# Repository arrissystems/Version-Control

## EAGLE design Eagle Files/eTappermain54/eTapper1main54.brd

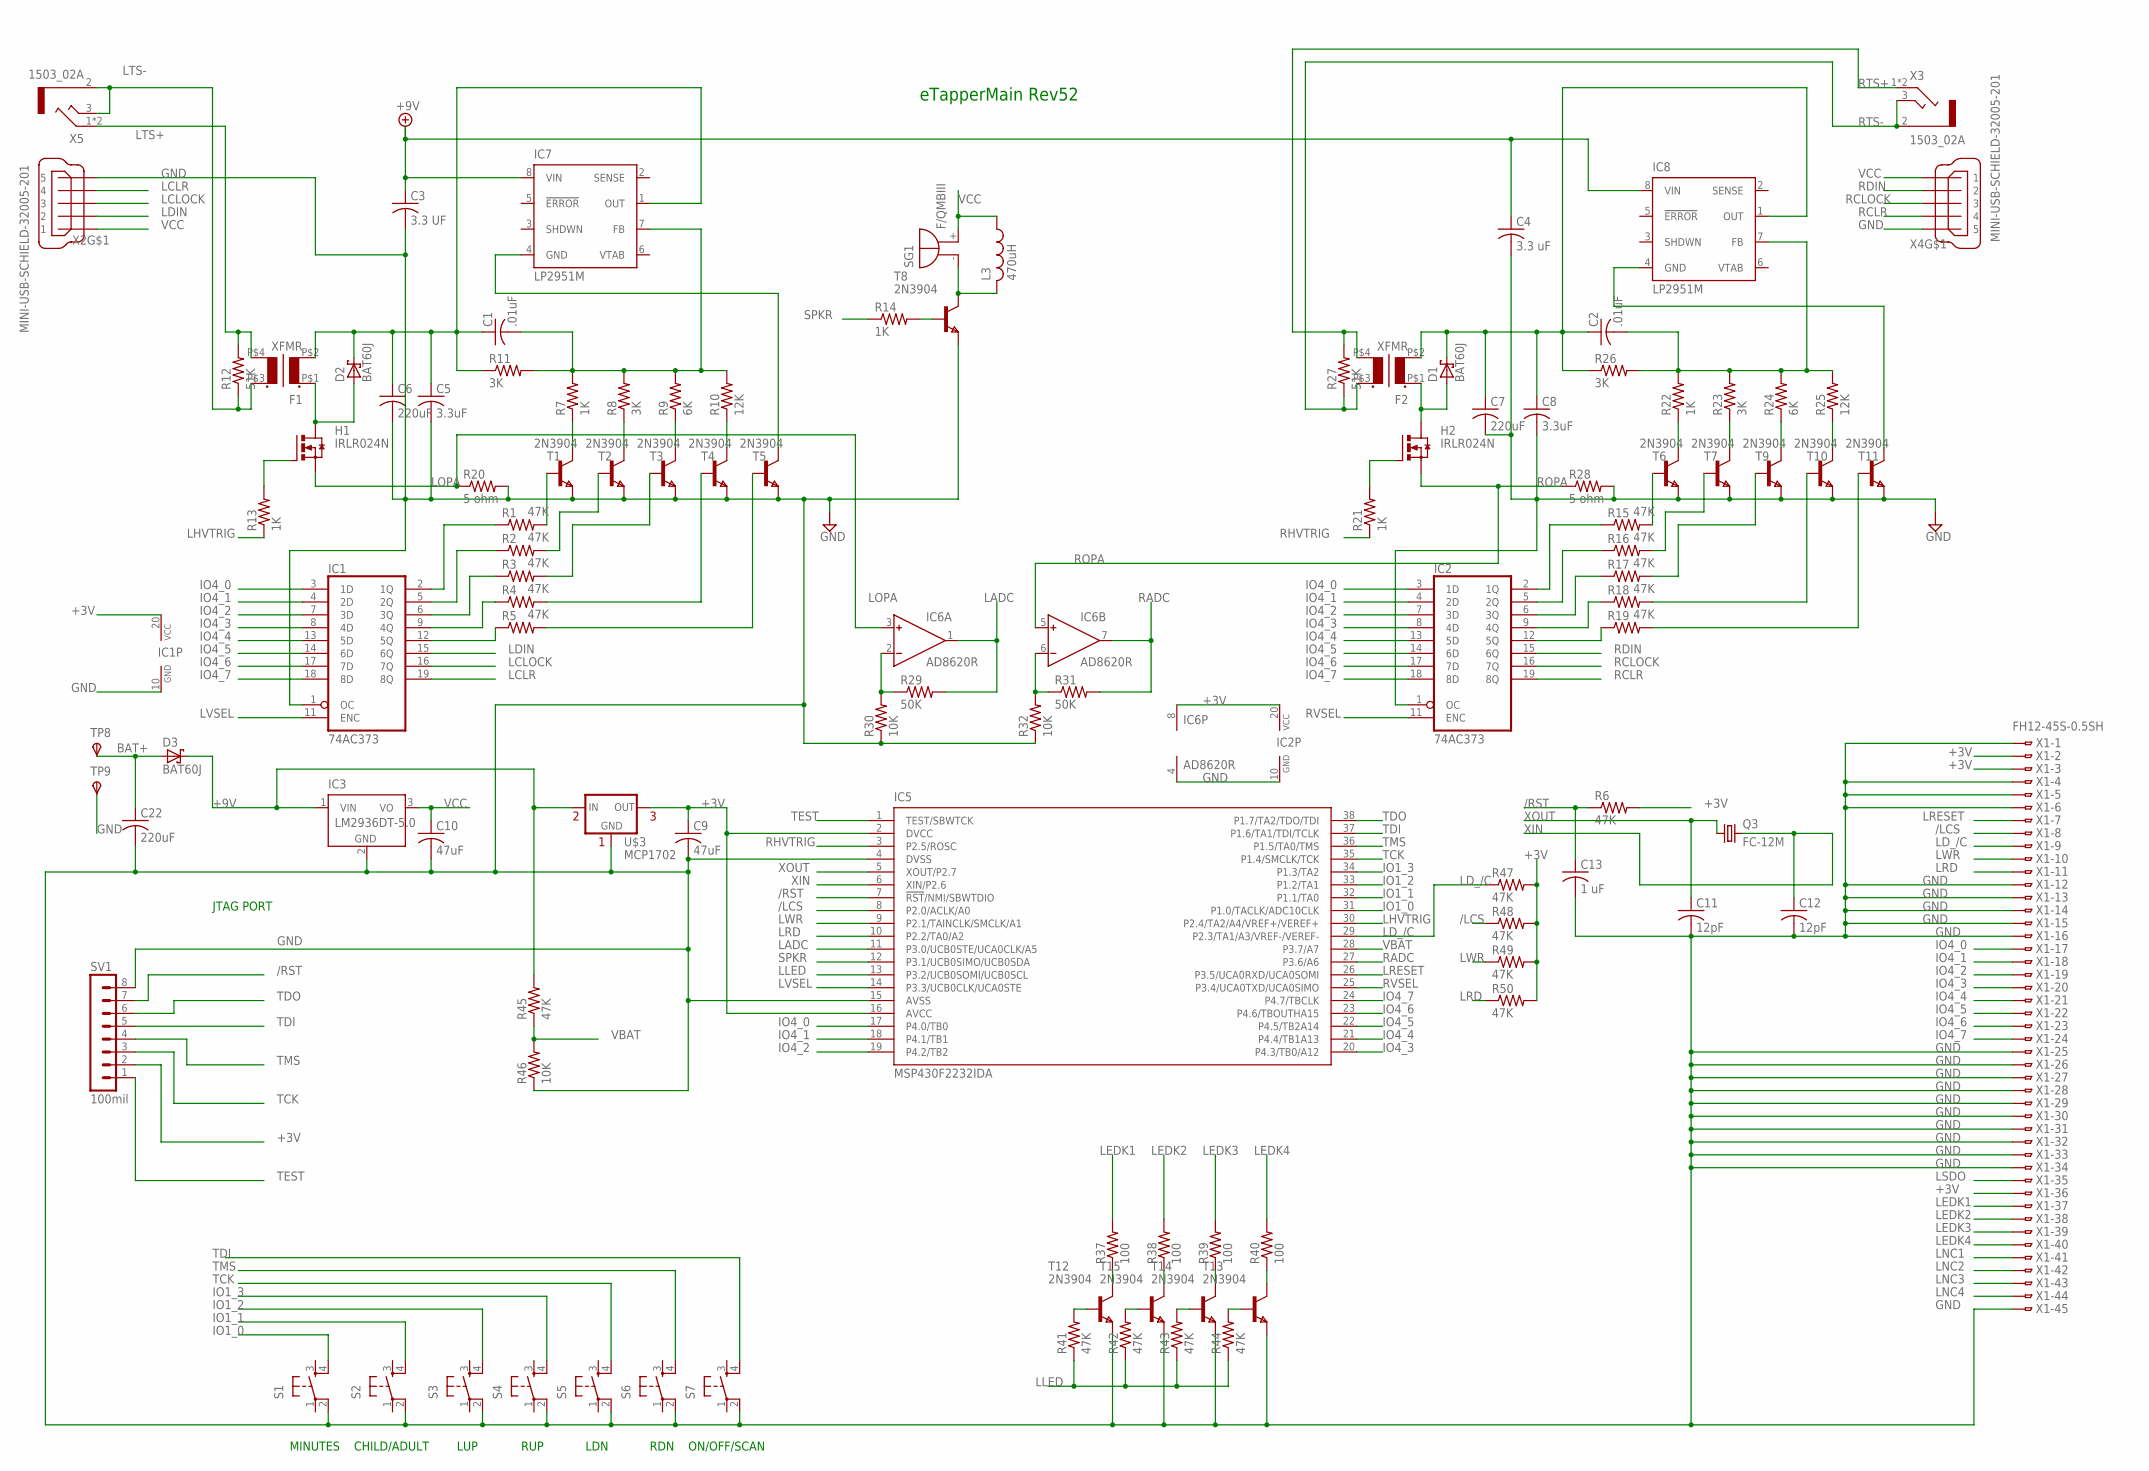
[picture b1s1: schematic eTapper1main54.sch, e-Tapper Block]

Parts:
C1, C2: .01uF; C0805
C3: 3.3 UF; C1206
C4: 3.3 uF; C1206
C5, C8: 3.3uF; C0805
C6, C7, C22: 220uF; C1206
C9, C10: 47uF; C1206
C11, C12: 12pF; C0805
C13: 1 uF; C0805
D1, D2, D3: BAT60J; SOD323_ST
F1, F2: XFMR
H1, H2: IRLR024N; D-PAK_TO252AA
IC1, IC2: 74AC373; SO20
IC3: LM2936DT-5.0; TO252
IC5: MSP430F2232IDA; TSSOP38_R-PDSO-G38-DA
IC6: AD8620R; SO8
IC7, IC8: LP2951M; SO08
L3: 470uH; L2825P
Q3: FC-12M
R1, R2, R3, R4, R5, R6, R15, R16, R17, R18, R19, R41, R42, R43, R44, R45, R47, R48, R49, R50: 47K; R0603
R7, R13, R14, R21, R22: 1K; R0603
R8, R11, R23, R26: 3K; R0603
R9, R24: 6K; R0603
R10, R25: 12K; R0603
R12, R27: 51K; R0603
R20, R28: 5 ohm; R0603
R29, R31: 50K; R0603
R30, R32, R46: 10K; R0603
R37, R38, R39, R40: 100; R0603
S1, S2, S3, S4, S5, S6, S7: 10-XX; B3F-10XX
SG1: F/QMBIII
SV1: 100mil; MA08-1
T1, T2, T3, T4, T5, T6, T7, T8, T9, T10, T11, T12, T13, T14, T15: 2N3904; SOT-23
TP8, TP9: TPSPAD1-20; P1-20
U$3: MCP1702; TO92-
X1: FH12-45S-0.5SH
X2, X4: MINI-USB-SCHIELD-32005-201; 32005-201
X3, X5: 1503_02A; 1503_02

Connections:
+3V: C9.1, IC1.20 (VCC), IC2.20 (VCC), IC5.2 (DVCC), IC5.16 (AVCC), IC6.8 (V+), R6.2, R47.2, R48.2, R49.2, R50.2, SV1.2, U$3.3 (OUT), X1.2, X1.3, X1.36
+9V: C3.1, C4.1, D3.C, IC3.1 (VIN), IC7.8 (VIN), IC8.8 (VIN), R45.2, U$3.2 (IN)
/LCS: IC5.8 (P2.0/ACLK/A0), R48.1, X1.8
/RST: C13.1, IC5.7 (!RST!/NMI/SBWTDIO), R6.1, SV1.7
BAT+: C22.1, D3.A, TP8.TP
GND: C3.2, C4.2, C5.2, C6.2, C7.2, C8.2, C9.2, C10.2, C11.2, C12.2, C13.2, C22.2, IC1.1 (OC), IC1.10 (GND), IC2.1 (OC), IC2.10 (GND), IC3.2 (GND), IC5.4 (DVSS), IC5.15 (AVSS), IC6.4 (V-), R20.2, R28.2, R30.1, R32.1, R46.1, S1.2 (P1), S2.2 (P1), S3.2 (P1), S4.2 (P1), S5.2 (P1), S6.2 (P1), S7.2 (P1), SV1.8, T1.2 (E), T2.2 (E), T3.2 (E), T4.2 (E), T5.2 (E), T6.2 (E), T7.2 (E), T8.2 (E), T9.2 (E), T10.2 (E), T11.2 (E), T12.2 (E), T13.2 (E), T14.2 (E), T15.2 (E), TP9.TP, U$3.1 (GND), X1.1, X1.4, X1.5, X1.6, X1.12, X1.13, X1.14, X1.15, X1.16, X1.25, X1.26, X1.27, X1.28, X1.29, X1.30, X1.31, X1.32, X1.33, X1.34, X1.45, X2.5, X4.5
IO1_0: IC5.31 (P1.0/TACLK/ADC10CLK), S1.4 (S1)
IO1_1: IC5.32 (P1.1/TA0), S2.4 (S1)
IO1_2: IC5.33 (P1.2/TA1), S3.4 (S1)
IO1_3: IC5.34 (P1.3/TA2), S4.4 (S1)
IO4_0: IC1.3 (1D), IC2.3 (1D), IC5.17 (P4.0/TB0), X1.17
IO4_1: IC1.4 (2D), IC2.4 (2D), IC5.18 (P4.1/TB1), X1.18
IO4_2: IC1.7 (3D), IC2.7 (3D), IC5.19 (P4.2/TB2), X1.19
IO4_3: IC1.8 (4D), IC2.8 (4D), IC5.20 (P4.3/TB0/A12), X1.20
IO4_4: IC1.13 (5D), IC2.13 (5D), IC5.21 (P4.4/TB1A13), X1.21
IO4_5: IC1.14 (6D), IC2.14 (6D), IC5.22 (P4.5/TB2A14), X1.22
IO4_6: IC1.17 (7D), IC2.17 (7D), IC5.23 (P4.6/TBOUTHA15), X1.23
IO4_7: IC1.18 (8D), IC2.18 (8D), IC5.24 (P4.7/TBCLK), X1.24
LADC: IC5.11 (P3.0/UCB0STE/UCA0CLK/A5), IC6.1 (OUT), R29.2
LCLOCK: IC1.16 (7Q), X2.3
LCLR: IC1.19 (8Q), X2.4
LDIN: IC1.15 (6Q), X2.2
LD_/C: IC5.29 (P2.3/TA1/A3/VREF-/VEREF-), R47.1, X1.9
LEDK1: R37.2, X1.37
LEDK2: R38.2, X1.38
LEDK3: R39.2, X1.39
LEDK4: R40.2, X1.40
LHVTRIG: IC5.30 (P2.4/TA2/A4/VREF+/VEREF+), R13.1
LLED: IC5.13 (P3.2/UCB0SOMI/UCB0SCL), R41.1, R42.1, R43.1, R44.1
LNC1: X1.41
LNC2: X1.42
LNC3: X1.43
LNC4: X1.44
LOPA: H1.3 (S), IC6.3 (IN+), R20.1
LRD: IC5.10 (P2.2/TA0/A2), R50.1, X1.11
LRESET: IC5.26 (P3.5/UCA0RXD/UCA0SOMI), X1.7
LSDO: X1.35
LTS+: F1.P$4 (S2), R12.2, X5.1 (2), X5.4 (2)
LTS-: F1.P$3 (S1), R12.1, X5.2 (1), X5.3
LVSEL: IC1.11 (ENC), IC5.14 (P3.3/UCB0CLK/UCA0STE)
LWR: IC5.9 (P2.1/TAINCLK/SMCLK/A1), R49.1, X1.10
unnamed: IC1.2 (1Q), R1.1
unnamed: IC1.5 (2Q), R2.1
unnamed: IC1.6 (3Q), R3.1
unnamed: IC1.9 (4Q), R4.1
unnamed: IC1.12 (5Q), R5.1
unnamed: L3.2, SG1.- (+), T8.1 (C)
unnamed: R4.2, T4.3 (B)
unnamed: R5.2, T5.3 (B)
unnamed: D2.A, F1.P$1 (P1), H1.4 (D)
unnamed: R7.1, T1.1 (C)
unnamed: R8.1, T2.1 (C)
unnamed: R9.1, T3.1 (C)
unnamed: R1.2, T1.3 (B)
unnamed: R2.2, T2.3 (B)
unnamed: R3.2, T3.3 (B)
unnamed: R10.1, T4.1 (C)
unnamed: C1.2, IC7.7 (FB), R7.2, R8.2, R9.2, R10.2, R11.2
unnamed: C1.1, C5.1, C6.1, D2.C, F1.P$2 (P2), IC7.1 (OUT), R11.1
unnamed: D1.A, F2.P$1 (P1), H2.4 (D)
unnamed: IC2.2 (1Q), R15.1
unnamed: H1.1 (G), R13.2
unnamed: R14.2, T8.3 (B)
unnamed: IC2.5 (2Q), R16.1
unnamed: IC2.6 (3Q), R17.1
unnamed: IC2.9 (4Q), R18.1
unnamed: IC2.12 (5Q), R19.1
unnamed: R44.2, T13.3 (B)
unnamed: R15.2, T6.3 (B)
unnamed: R16.2, T7.3 (B)
unnamed: R17.2, T9.3 (B)
unnamed: R18.2, T10.3 (B)
unnamed: R19.2, T11.3 (B)
unnamed: R22.1, T6.1 (C)
unnamed: R23.1, T7.1 (C)
unnamed: R24.1, T9.1 (C)
unnamed: R25.1, T10.1 (C)
unnamed: C2.2, IC8.7 (FB), R22.2, R23.2, R24.2, R25.2, R26.2
unnamed: C2.1, C7.1, C8.1, D1.C, F2.P$2 (P2), IC8.1 (OUT), R26.1
unnamed: R37.1, T12.1 (C)
unnamed: H2.1 (G), R21.2
unnamed: R38.1, T15.1 (C)
unnamed: R39.1, T14.1 (C)
unnamed: IC7.4 (GND), T5.1 (C)
unnamed: R40.1, T13.1 (C)
unnamed: IC8.4 (GND), T11.1 (C)
unnamed: R43.2, T14.3 (B)
unnamed: R41.2, T12.3 (B)
unnamed: R42.2, T15.3 (B)
unnamed: IC6.6 (IN-), R31.1, R32.2
unnamed: IC6.2 (IN-), R29.1, R30.2
RADC: IC5.27 (P3.6/A6), IC6.7 (OUT), R31.2
RCLOCK: IC2.16 (7Q), X4.3
RCLR: IC2.19 (8Q), X4.4
RDIN: IC2.15 (6Q), X4.2
RHVTRIG: IC5.3 (P2.5/ROSC), R21.1
ROPA: H2.3 (S), IC6.5 (IN+), R28.1
RTS+: F2.P$4 (S2), R27.2, X3.1 (2), X3.4 (2)
RTS-: F2.P$3 (S1), R27.1, X3.2 (1), X3.3
RVSEL: IC2.11 (ENC), IC5.25 (P3.4/UCA0TXD/UCA0SIMO)
SPKR: IC5.12 (P3.1/UCB0SIMO/UCB0SDA), R14.1
TCK: IC5.35 (P1.4/SMCLK/TCK), S5.4 (S1), SV1.3
TDI: IC5.37 (P1.6/TA1/TDI/TCLK), S7.4 (S1), SV1.5
TDO: IC5.38 (P1.7/TA2/TDO/TDI), SV1.6
TEST: IC5.1 (TEST/SBWTCK), SV1.1
TMS: IC5.36 (P1.5/TA0/TMS), S6.4 (S1), SV1.4
VBAT: IC5.28 (P3.7/A7), R45.1, R46.2
VCC: C10.1, IC3.3 (VO), L3.1, SG1.+ (-), X2.1, X4.1
XIN: C12.1, IC5.6 (XIN/P2.6), Q3.2
XOUT: C11.1, IC5.5 (XOUT/P2.7), Q3.1

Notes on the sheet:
ON/OFF/SCAN
MINUTES
CHILD/ADULT
LUP
RUP
JTAG PORT
LDN
RDN
eTapperMain Rev52

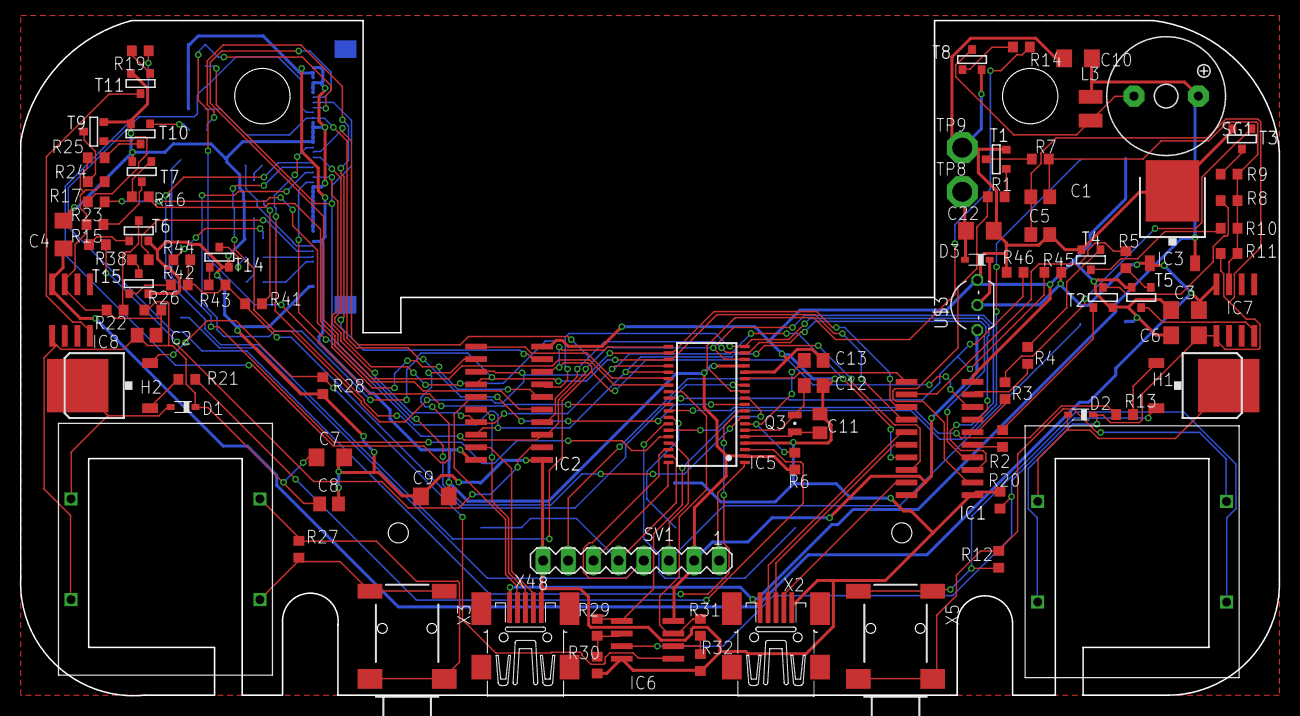
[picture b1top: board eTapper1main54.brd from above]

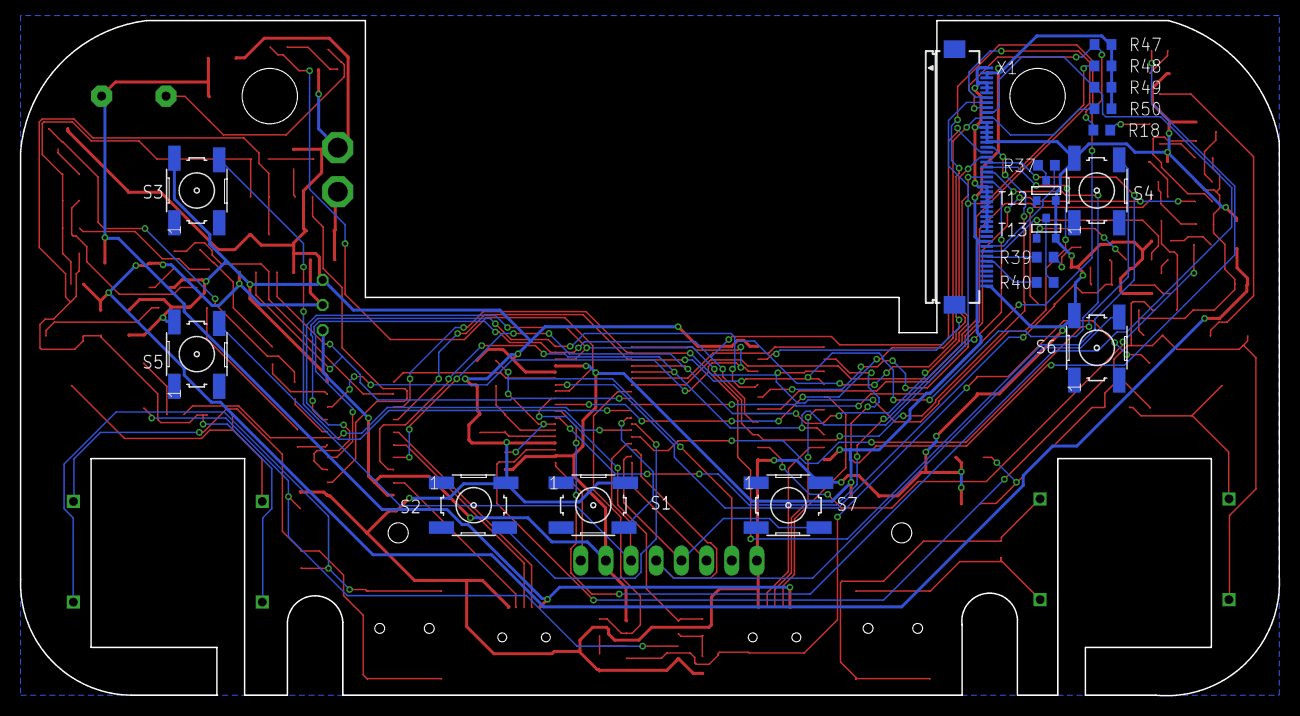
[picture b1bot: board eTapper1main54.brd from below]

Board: 2 copper layers, 127.0 x 68.1 mm, 109 parts (18 on the bottom side), 105 nets.

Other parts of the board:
DRILEGEND: DRILEGEND
